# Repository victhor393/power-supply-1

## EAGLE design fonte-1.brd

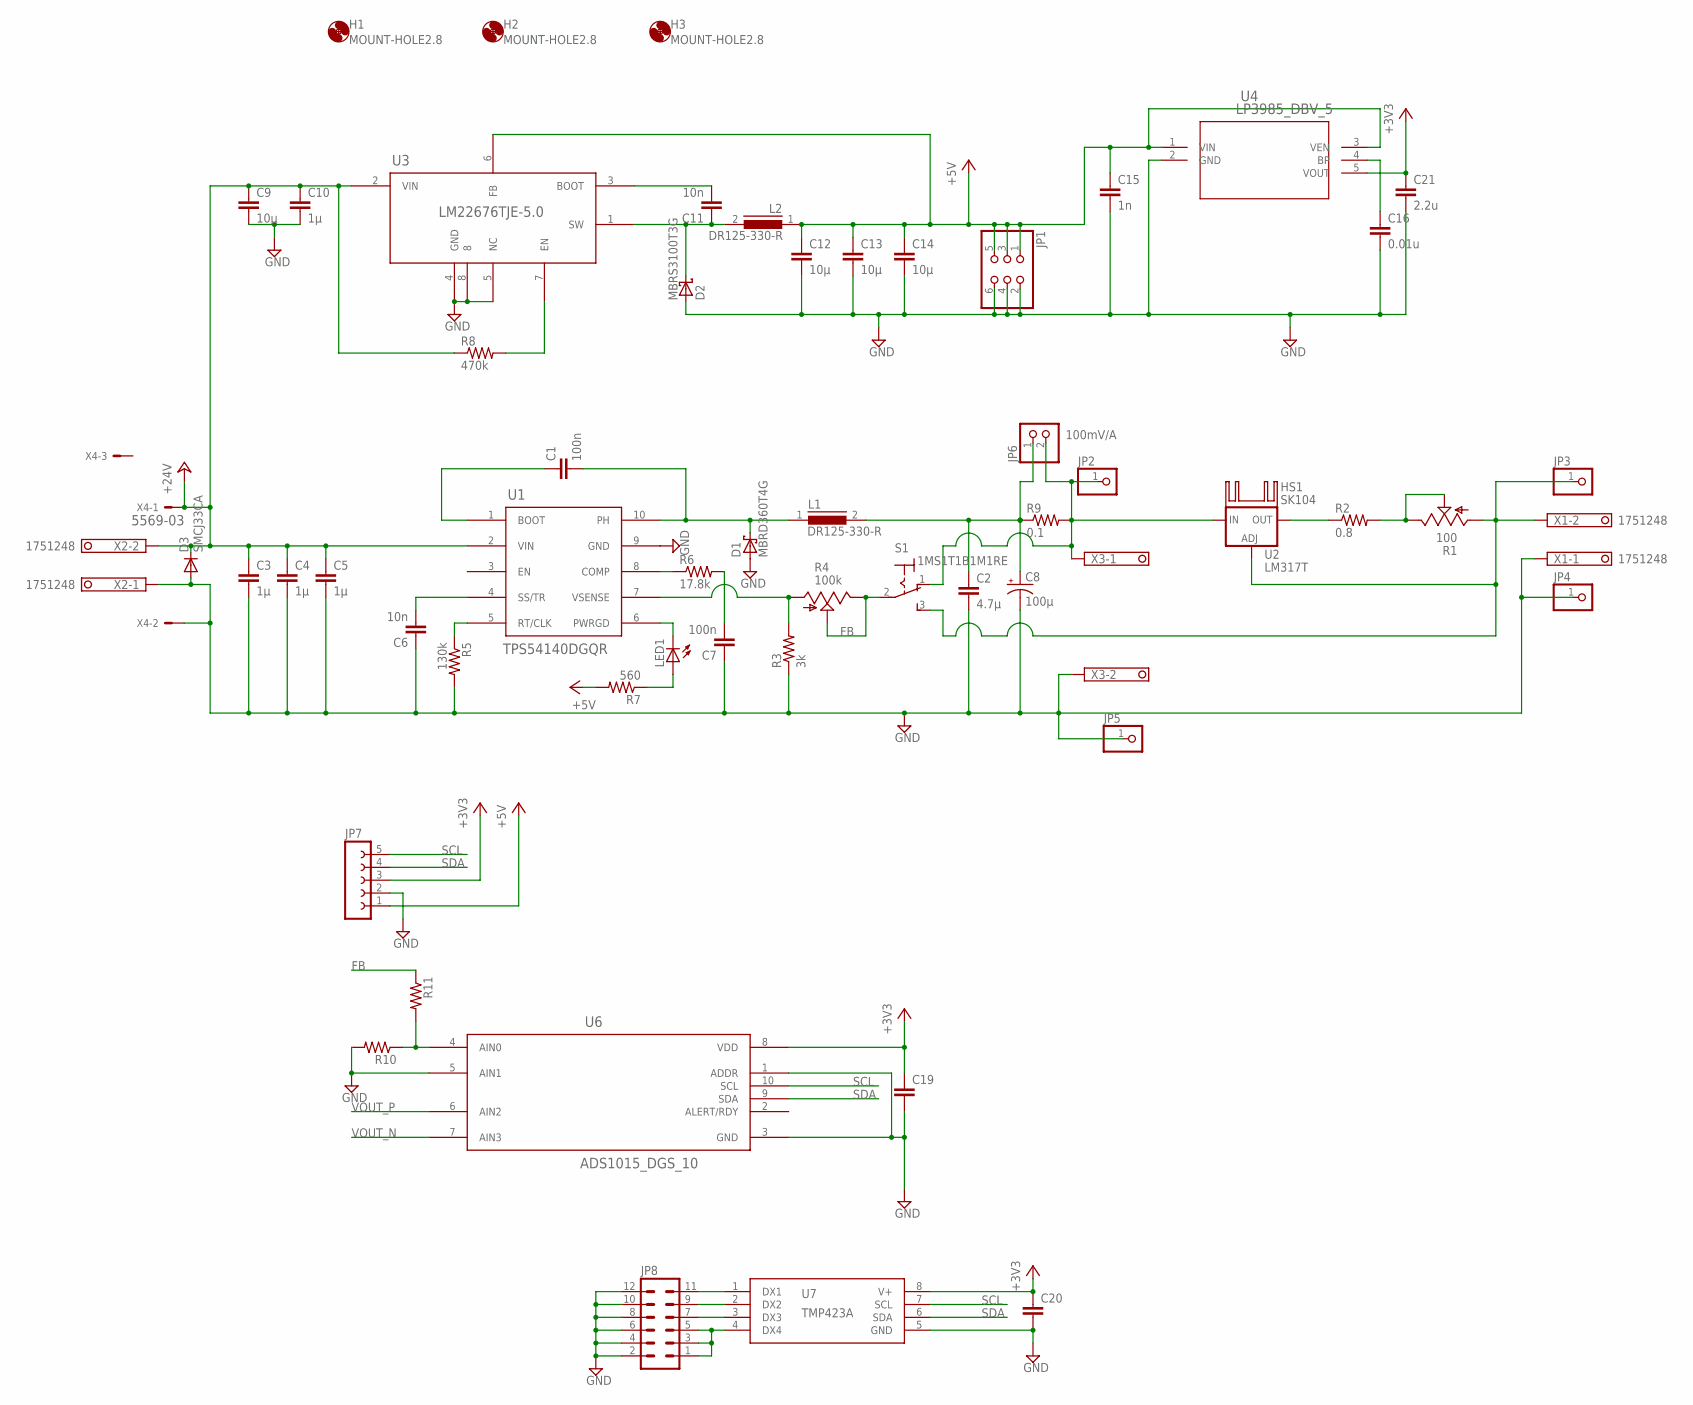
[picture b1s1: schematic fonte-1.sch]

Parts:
C1, C7: 100n; C0805
C2: 4.7µ; C1210
C3, C4, C5, C10: 1µ; C1206
C6, C11: 10n; C0805
C8: 100µ; UD-8X10_NICHICON
C9: 10µ; C2220K
C12, C13, C14: 10µ; C1206
C15: 1n; C0805
C16: 0.01u; C0805
C19: C-EUC0805; C0805
C20: C-EUC1206; C1206
C21: 2.2u; C0805
D1: MBRD360T4G; DPACK_1
D2: MBRS3100T3G; SMC
D3: SMCJ33CA; SMC
H1, H2, H3: MOUNT-HOLE2.8; 2,8
HS1: SK104
JP1: PINHD-2X3; 2X03
JP2, JP3, JP4, JP5: PINHD-1X1; 1X01
JP6: 100mV/A; 1X02
JP7: FE05-1
JP8: MA06-2
L1, L2: DR125-330-R; DR125
LED1: LED5MM
R1: 100; 1X03
R2: 0.8; R2512
R3: 3k; R0805
R4: 100k; 1X03
R5: 130k; R0805
R6: 17.8k; R0805
R7: 560; R0805
R8: 470k; R0805
R9: 0.1; R2010
R10, R11: R-US_R0805; R0805
S1: 1MS1T1B1M1RE; M9040P
U1: TPS54140DGQR; DGQ10_1P88X1P57
U2: LM317T; 317TS
U3: LM22676TJE-5.0; TJ7A
U4: LP3985_DBV_5; MF05A
U6: ADS1015_DGS_10; DGS10
U7: TMP423A; SOT23-8
X1, X2, X3: 1751248
X4: 5569-03

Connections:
+3V3: C19.1, C20.1, C21.1, JP7.3, U4.5 (VOUT), U6.8 (VDD), U7.8 (V+)
+5V: C12.1, C13.1, C14.1, C15.1, JP1.1, JP1.3, JP1.5, JP7.1, L2.1, R7.2, U3.6 (FB), U4.1 (VIN), U4.3 (VEN)
+24V: C3.1, C4.1, C5.1, C9.1, C10.1, D3.C, R8.1, U1.2 (VIN), U3.2 (VIN), X2.2, X4.1
FB: R4.2 (S), R4.3 (E), R11.1, S1.2
GND: C2.2, C3.2, C4.2, C5.2, C6.1, C7.1, C8.-, C9.2, C10.2, C12.2, C13.2, C14.2, C15.2, C16.2, C19.2, C20.2, C21.2, D1.A1 (A), D1.A2 (A), D2.A, D3.A, JP1.2, JP1.4, JP1.6, JP4.1, JP5.1, JP7.2, JP8.2, JP8.4, JP8.6, JP8.8, JP8.10, JP8.12, R3.1, R5.2, R10.2, U1.9 (GND), U3.4 (GND), U3.5 (NC), U3.8, U4.2 (GND), U6.1 (ADDR), U6.3 (GND), U6.5 (AIN1), U7.5 (GND), X1.1, X2.1, X3.2, X4.2
unnamed: C1.2, D1.K (C), L1.1, U1.10 (PH)
unnamed: C1.1, U1.1 (BOOT)
unnamed: R1.2 (S), R1.3 (E), R2.2
unnamed: R8.2, U3.7 (EN)
unnamed: R10.1, R11.2, U6.4 (AIN0)
unnamed: R2.1, U2.2 (OUT)
unnamed: R3.2, R4.1 (A), U1.7 (VSENSE)
unnamed: JP8.1, JP8.3, JP8.5, U7.4 (DX4)
unnamed: R5.1, U1.5 (RT/CLK)
unnamed: C6.2, U1.4 (SS/TR)
unnamed: R6.1, U1.8 (COMP)
unnamed: C7.2, R6.2
unnamed: LED1.K (C), U1.6 (PWRGD)
unnamed: LED1.A, R7.1
unnamed: C16.1, U4.4 (BP)
unnamed: C11.1, D2.C, L2.2, U3.1 (SW)
unnamed: JP8.7, U7.3 (DX3)
unnamed: C11.2, U3.3 (BOOT)
unnamed: JP8.9, U7.2 (DX2)
unnamed: JP8.11, U7.1 (DX1)
SCL: JP7.5, U6.10 (SCL), U7.7 (SCL)
SDA: JP7.4, U6.9 (SDA), U7.6 (SDA)
VOUT_CC: JP3.1, R1.1 (A), S1.3 (S), U2.1 (ADJ), X1.2
VOUT_N: JP2.1, JP6.2, R9.2, S1.1 (O), U2.3 (IN), U6.7 (AIN3), X3.1
VOUT_P: C2.1, C8.+, JP6.1, L1.2, R9.1, U6.6 (AIN2)

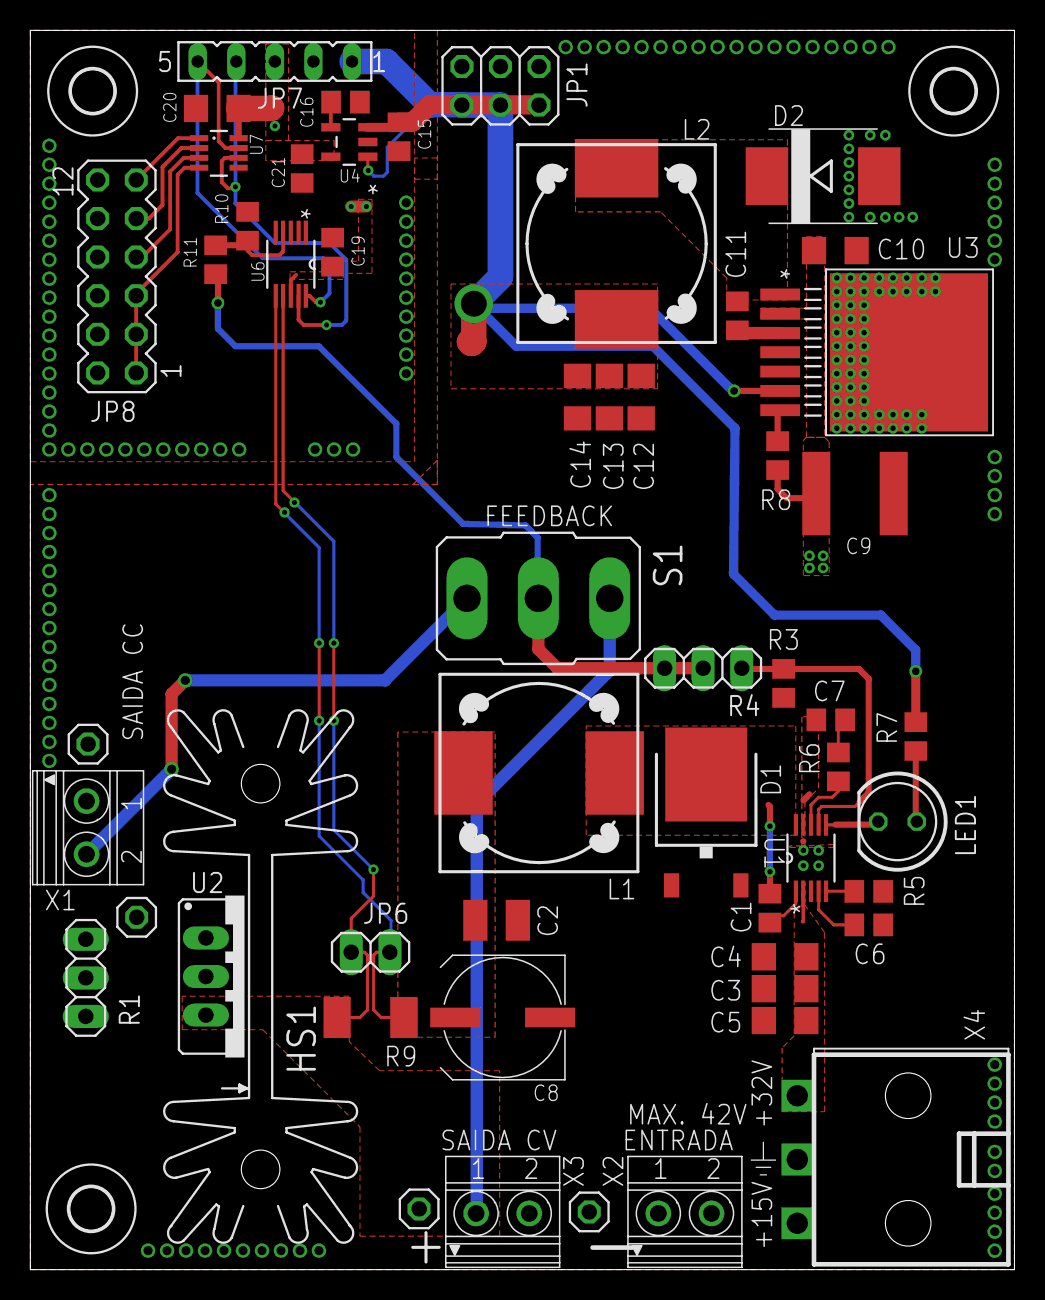
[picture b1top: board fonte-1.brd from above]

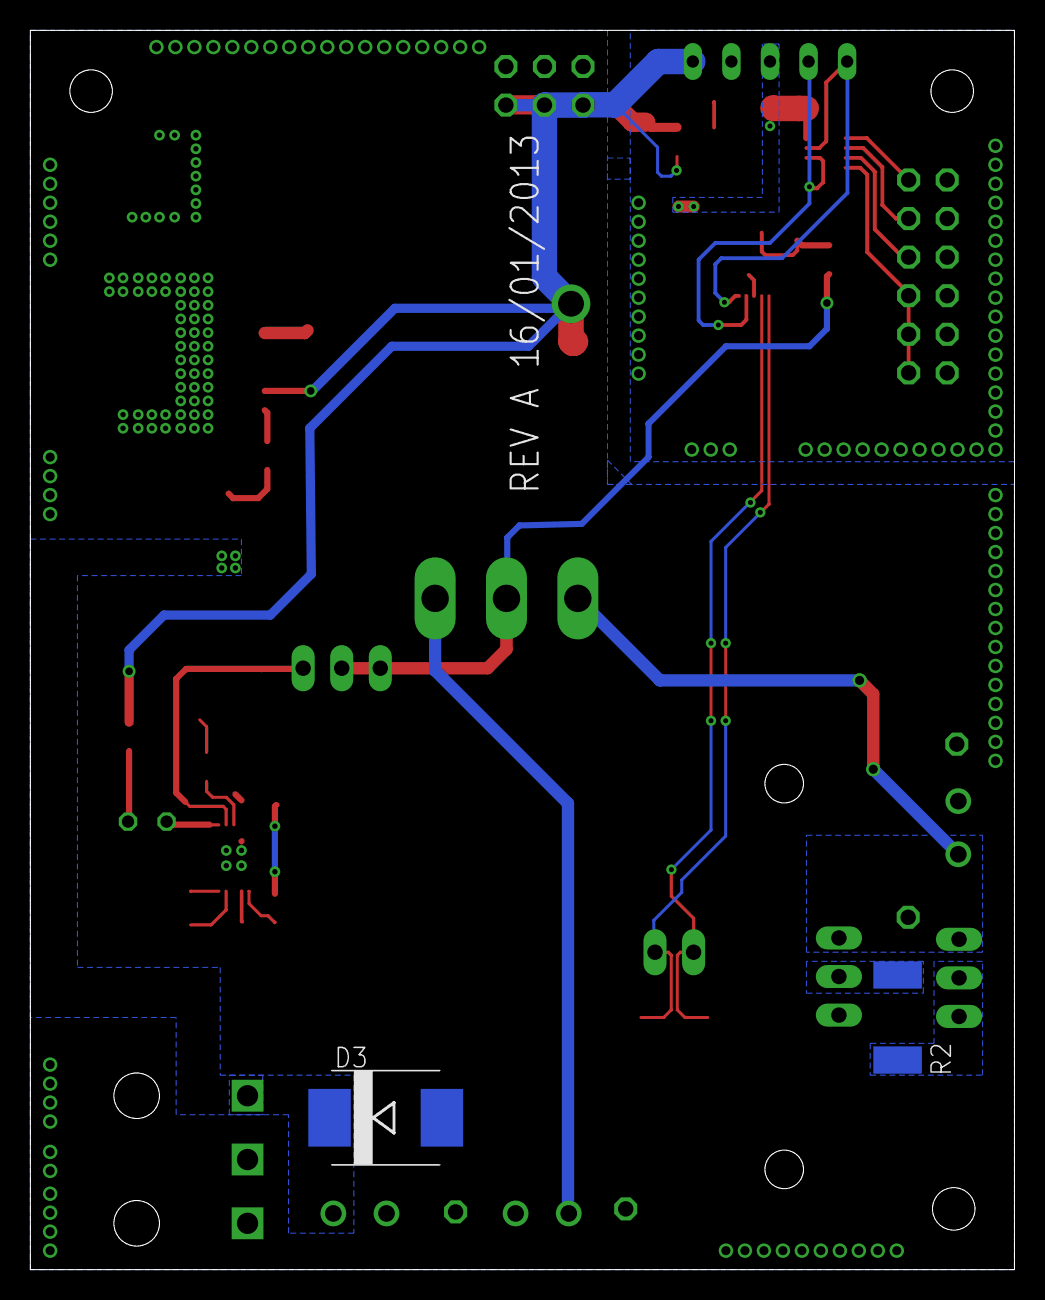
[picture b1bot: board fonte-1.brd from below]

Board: 2 copper layers, 64.8 x 81.6 mm, 60 parts (2 on the bottom side), 30 nets.

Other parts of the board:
U$1: GND

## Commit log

2019-05-12 Initial commit fix
2019-05-21 Added schematic and board layout in pdf format
